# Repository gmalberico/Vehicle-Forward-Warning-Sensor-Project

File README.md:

# Wireless Forward-Obstacle Warning System

A compact vehicle-mounted prototype that uses LiDAR ranging and wireless communication to warn a driver when an object is detected ahead.

The system is split into two units:

- A **sensor/transmitter unit** mounted toward the front of the vehicle
- A **receiver/warning unit** located near the driver

The sensor unit measures distance using a TF-Luna LiDAR, processes the reading with an Arduino Nano, and transmits warning data over an nRF24L01 radio link. The receiver listens for the message and activates an indicator when an obstacle is inside the configured warning range.

> **Status:** Active hardware and firmware development

---

## System Overview

```text
TF-Luna LiDAR
      |
      | I2C
      v
Arduino Nano
      |
      | SPI
      v
nRF24L01 Transmitter
      |
      | 2.4 GHz wireless link
      v
nRF24L01 Receiver
      |
      | SPI
      v
Arduino Nano
      |
      v
Warning Indicator
```

The sensor node is intended to operate from a rechargeable battery charged by a small solar panel.

---

## Features

- Forward distance measurement using a TF-Luna LiDAR
- Wireless warning transmission using nRF24L01 modules
- Arduino Nano-based control on both ends
- Packet acknowledgement support
- Configurable distance threshold
- Receiver-side warning LED
- Solar-assisted battery charging
- Custom PCB development in KiCad
- Separate radio, LiDAR, power, and firmware test configurations

---

## Hardware

### Sensor / Transmitter Unit

- Arduino Nano V3
- DFRobot TF-Luna ToF Micro Single-Point Ranging LiDAR
- nRF24L01 2.4 GHz transceiver
- TI BQ25306 battery charger
- Two-cell rechargeable battery system
- DFRobot FIT0330 9 V, 600 mA solar panel
- 3.3 V regulation for the radio
- External LiDAR connector
- Charging-status LED
- Custom PCB

### Receiver Unit

- Arduino Nano V3
- nRF24L01 2.4 GHz transceiver
- Warning LED or other indicator
- Regulated power source

---

## Electrical Interfaces

### TF-Luna LiDAR

The TF-Luna is used as an off-board sensor head.

| Signal | Connection |
|---|---|
| Power | 5 V |
| Ground | GND |
| SDA | Arduino Nano A4 |
| SCL | Arduino Nano A5 |

The I2C bus uses approximately **3 kΩ pull-up resistors to 3.3 V**.

### nRF24L01

The nRF24L01 communicates with the Arduino Nano over SPI.

| nRF24L01 Pin | Arduino Nano |
|---|---|
| VCC | Regulated 3.3 V |
| GND | GND |
| CE | Firmware-defined GPIO |
| CSN | Firmware-defined GPIO |
| SCK | D13 |
| MOSI | D11 |
| MISO | D12 |
| IRQ | Optional |

The nRF24L01 must be powered from a stable 3.3 V rail. A local bypass capacitor should be placed close to the module.

**Do not connect 5 V directly to the nRF24L01 VCC pin.**

---

## Battery Charging System

The sensor node uses a TI BQ25306 charger configured for a two-cell Li-ion battery.

Current design values include:

| Parameter | Value |
|---|---:|
| Charge voltage | Approximately 8.4 V |
| Feedback upper resistor | 1.33 MΩ |
| Feedback lower resistor | 200 kΩ |
| BAT-to-FB capacitor | 470 pF |
| Inductor | 2.2 µH |
| BAT capacitor | 10 µF |
| PMID capacitor | 10 µF |
| VBUS capacitor | 2.2 µF |
| REGN capacitor | 2.2 µF |
| Charge-current resistor | 78.7 kΩ |

The selected 9 V, 600 mA solar panel is electrically compatible with the charger, but available charging current depends strongly on lighting conditions and panel orientation.

---

## Firmware Operation

### Transmitter

The transmitter firmware is intended to:

1. Initialize the TF-Luna and nRF24L01.
2. Read the measured distance.
3. Compare the distance with the warning threshold.
4. Transmit the distance and warning state.
5. Check for a returned acknowledgement.
6. Indicate successful or failed transmission when required.

### Receiver

The receiver firmware is intended to:

1. Initialize the nRF24L01.
2. Listen for incoming packets.
3. Validate received data.
4. Activate the warning indicator when the warning condition is true.
5. Turn the indicator off when the path is clear.
6. Enter a safe state when received data becomes stale.

## Current Development Priorities

- Improve packet and acknowledgement reliability
- Confirm stable 3.3 V radio power during transmission
- Finalize CE and CSN pin assignments
- Validate TF-Luna communication on the completed PCB
- Add packet timeout and fail-safe behavior
- Measure total current consumption
- Test solar charging under realistic conditions
- Confirm connector and 30 AWG wire compatibility
- Complete enclosure and weather-resistance design
- Perform controlled vehicle-mounted testing

---

## KiCad Files

The hardware design is developed in KiCad. Important project files include:

```text
*.kicad_pro
*.kicad_sch
*.kicad_pcb
*.kicad_sym
*.kicad_mod
*.pretty/
```

A suggested `.gitignore` for KiCad is:

```gitignore
# KiCad backups and temporary files
*-backups/
_autosave-*
*.lck
*.bak
*.tmp
fp-info-cache

# Operating-system files
.DS_Store
Thumbs.db
```

---

## Uploading Changes

After editing the project locally:

```bash
git status
git add .
git commit -m "Describe the changes"
git push
```

Before starting work on another computer:

```bash
git pull
```

---

## Safety Notice

This project is an experimental driver-assistance prototype.

It is not a certified automotive safety device and must not be relied upon as the sole method of obstacle detection, collision avoidance, or driver warning. Testing should be performed in a controlled environment before any vehicle-mounted use.

---

## Author

Gianni Alberico

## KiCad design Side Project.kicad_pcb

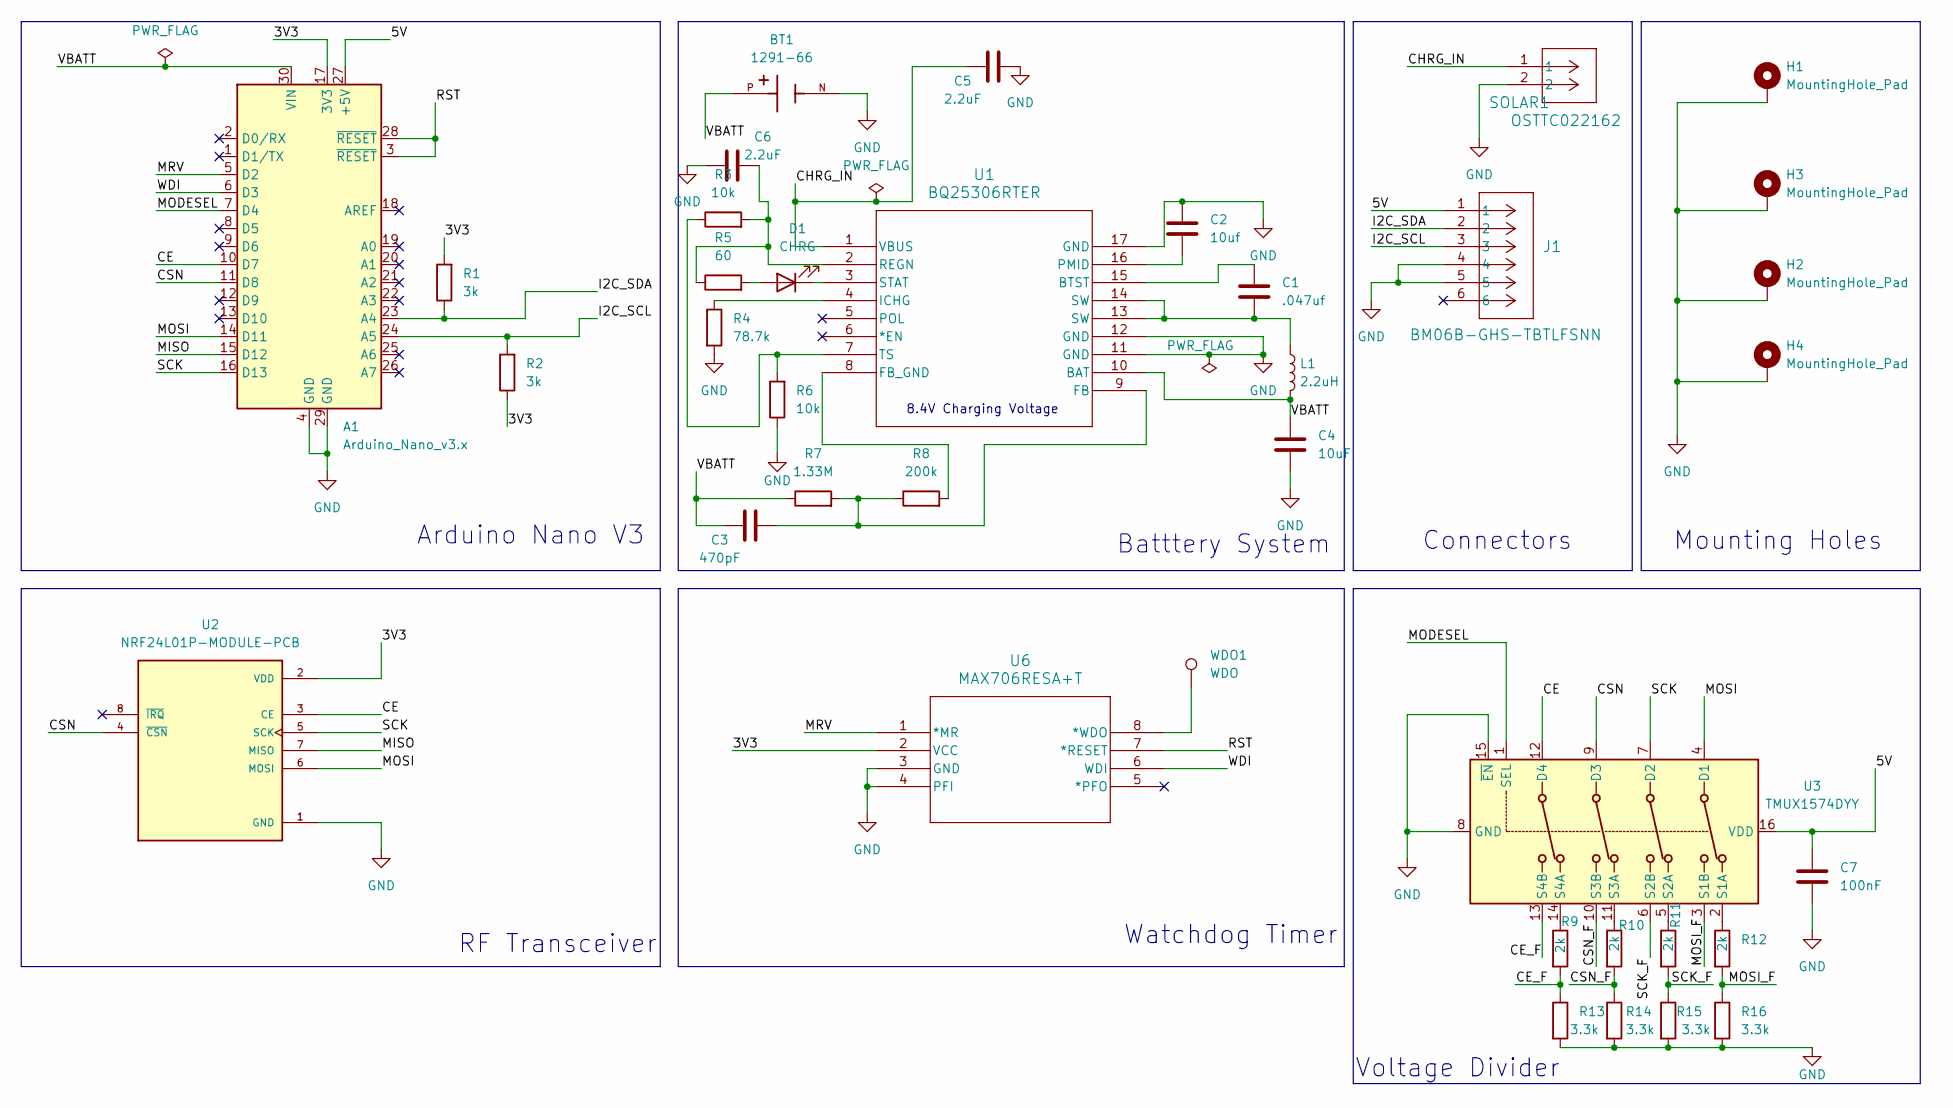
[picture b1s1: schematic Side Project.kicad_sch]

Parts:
A1: Arduino_Nano_v3.x; Arduino_Nano
BT1: 1291-66; BAT_1291-66; PARTREV A
C1: .047uf; C_0805_2012Metric
C2: 10uf; C_0805_2012Metric
C3: 470pF; C_0805_2012Metric
C4: 10uF; C_0805_2012Metric
C5, C6: 2.2uF; C_0805_2012Metric
C7: 100nF; C_0805_2012Metric
D1: CHRG; LED_0805_2012Metric
H1, H2, H3, H4: MountingHole_Pad; MountingHole_3.2mm_M3_Pad
J1: BM06B-GHS-TBTLFSNN; CONN_BM06B-GHS-TBT_JST
L1: 2.2uH; L_0805_2012Metric
R1, R2: 3k; R_0805_2012Metric
R3, R6: 10k; R_0805_2012Metric
R4: 78.7k; R_0805_2012Metric
R5: 60; R_0805_2012Metric
R7: 1.33M; R_0805_2012Metric
R8: 200k; R_0805_2012Metric
R9, R10, R11, R12: 2k; R_0805_2012Metric
R13, R14, R15, R16: 3.3k; R_0805_2012Metric
SOLAR1: OSTTC022162; CONN_OSTTC022162_OST
U1: BQ25306RTER; WQFN16_RTE_TEX
U2: NRF24L01P-MODULE-PCB; XCVR_NRF24L01P-MODULE-PCB; PARTREV 1.0
U3: TMUX1574DYY; Texas_DYY0016A_TSOT-23-16_2x4.2mm_P0.5mm
U6: MAX706RESA+T; 21-0041B_8_MXM-L
WDO1: WDO; TestPoint_THTPad_D3.0mm_Drill1.5mm

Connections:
/3V3: A1.17 (3V3), R1.2, R2.1, U2.2 (VDD), U6.2 (VCC)
/5V: A1.27 (+5V), C7.1, J1.1, U3.16 (VDD)
/CE: A1.10 (D7), U2.3 (CE), U3.12 (D4)
/CE_F: R9.2, R13.1, U3.13 (S4B)
/CHRG_IN: C5.1, SOLAR1.1, U1.1 (VBUS)
/CSN: A1.11 (D8), U2.4 (~CSN), U3.9 (D3)
/CSN_F: R10.2, R14.1, U3.10 (S3B)
/I2C_SCL: A1.24 (A5), J1.3, R2.2
/I2C_SDA: A1.23 (A4), J1.2, R1.1
/MISO: A1.15 (D12), U2.7 (MISO)
/MODESEL: A1.7 (D4), U3.1 (SEL)
/MOSI: A1.14 (D11), U2.6 (MOSI), U3.4 (D1)
/MOSI_F: R12.2, R16.1, U3.3 (S1B)
/MRV: A1.5 (D2), U6.1 (*MR)
/RST: A1.3 (~RESET), A1.28 (~RESET), U6.7 (*RESET)
/SCK: A1.16 (D13), U2.5 (SCK), U3.7 (D2)
/SCK_F: R11.2, R15.1, U3.6 (S2B)
/VBATT: A1.30 (VIN), BT1.P, C3.1, C4.1, L1.2, R7.1, U1.10 (BAT)
/WDI: A1.6 (D3), U6.6 (WDI)
GND: A1.4 (GND), A1.29 (GND), BT1.N, C2.1, C4.2, C5.2, C6.1, C7.2, H1.1, H2.1, H3.1, H4.1, J1.4, J1.5, R4.2, R6.1, R13.2, R14.2, R15.2, R16.2, SOLAR1.2, U1.11 (GND), U1.12 (GND), U1.17 (GND), U2.1 (GND), U3.8 (GND), U3.15 (~EN), U6.3 (GND), U6.4 (PFI)
unnamed: C1.2, L1.1, U1.13 (SW), U1.14 (SW)
unnamed: D1.2 (A), R5.2
unnamed: D1.1 (K), U1.3 (STAT)
unnamed: C1.1, U1.15 (BTST)
unnamed: C3.2, R7.2, R8.1, U1.9 (FB)
unnamed: R8.2, U1.8 (FB_GND)
unnamed: R4.1, U1.4 (ICHG)
unnamed: C2.2, U1.16 (PMID)
unnamed: C6.2, R3.2, R5.1, U1.2 (REGN)
unnamed: R3.1, R6.2, U1.7 (TS)
unnamed: R12.1, U3.2 (S1A)
unnamed: R11.1, U3.5 (S2A)
unnamed: R10.1, U3.11 (S3A)
unnamed: R9.1, U3.14 (S4A)
unnamed: U6.8 (*WDO), WDO1.1

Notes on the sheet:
Connectors
8.4V Charging Voltage
Mounting Holes
Watchdog Timer
Batttery System
Arduino Nano V3
RF Transceiver
Voltage Divider

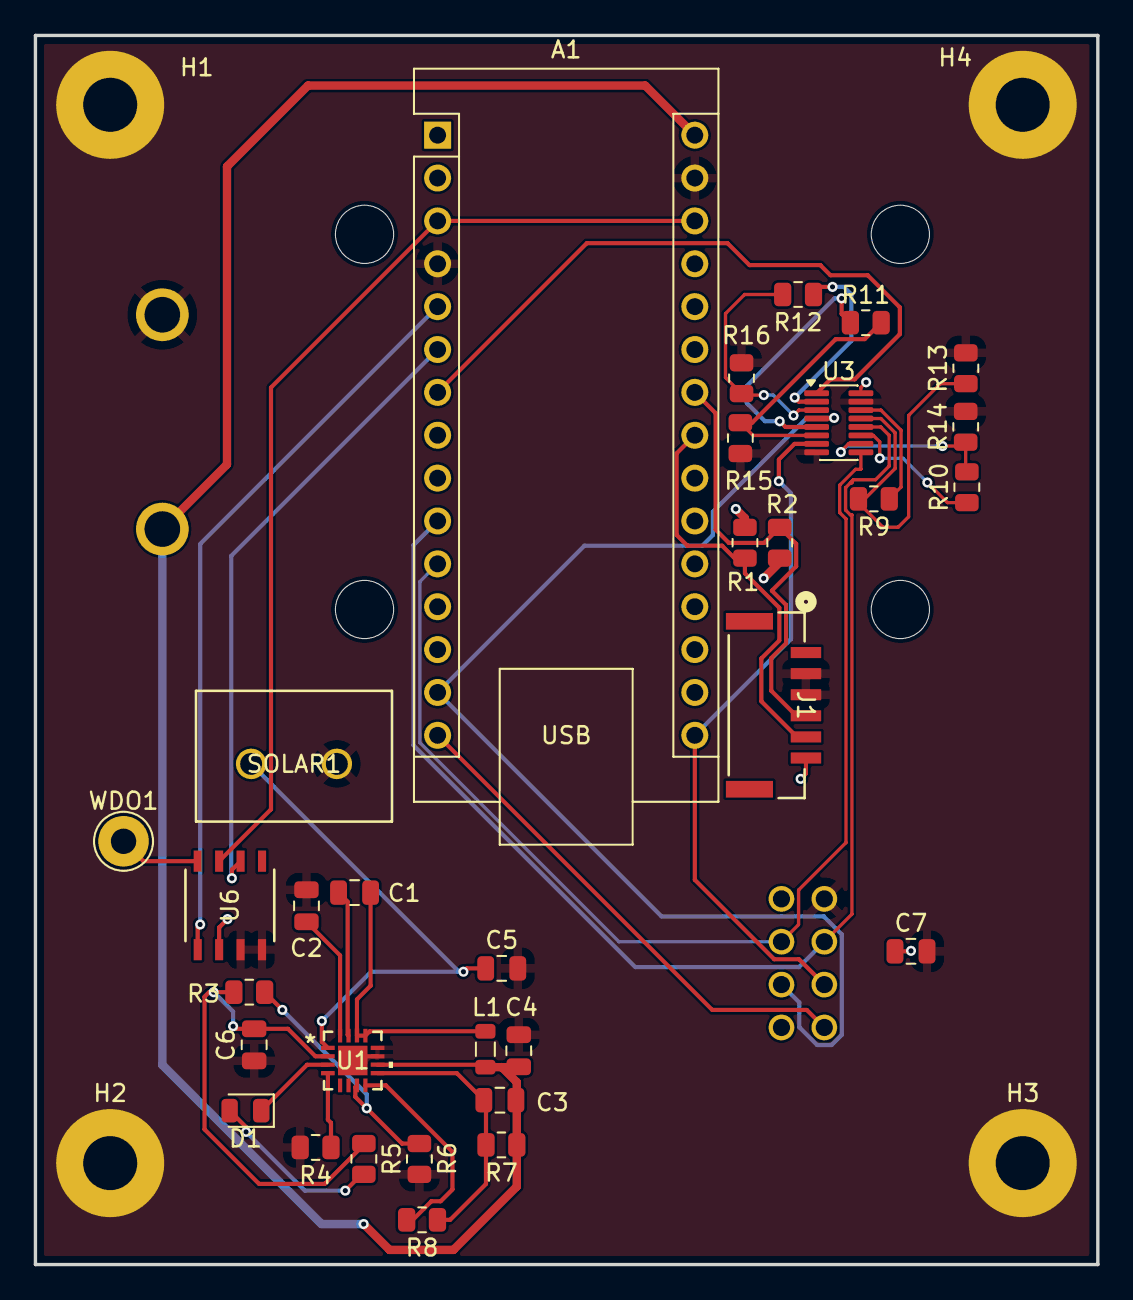
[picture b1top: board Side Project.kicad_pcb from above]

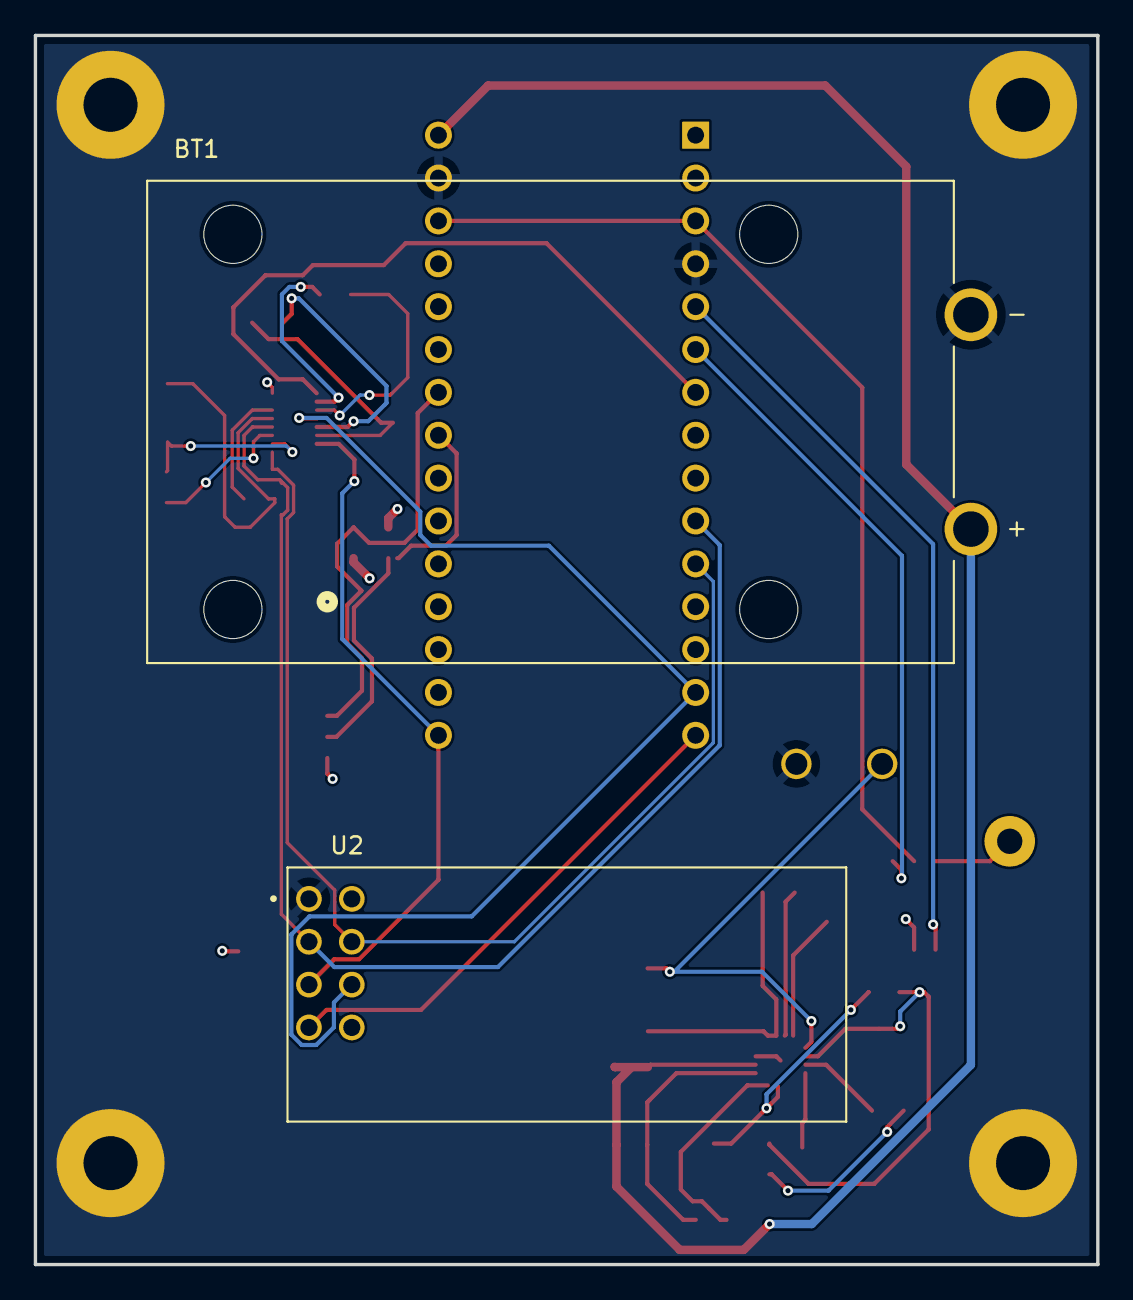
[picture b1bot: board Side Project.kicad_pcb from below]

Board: 4 copper layers, 63.0 x 72.8 mm, 38 parts (2 on the bottom side), 35 nets.
